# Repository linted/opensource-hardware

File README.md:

# opensource-hardware
Hardware creations for the masses

These files are under no warenty.

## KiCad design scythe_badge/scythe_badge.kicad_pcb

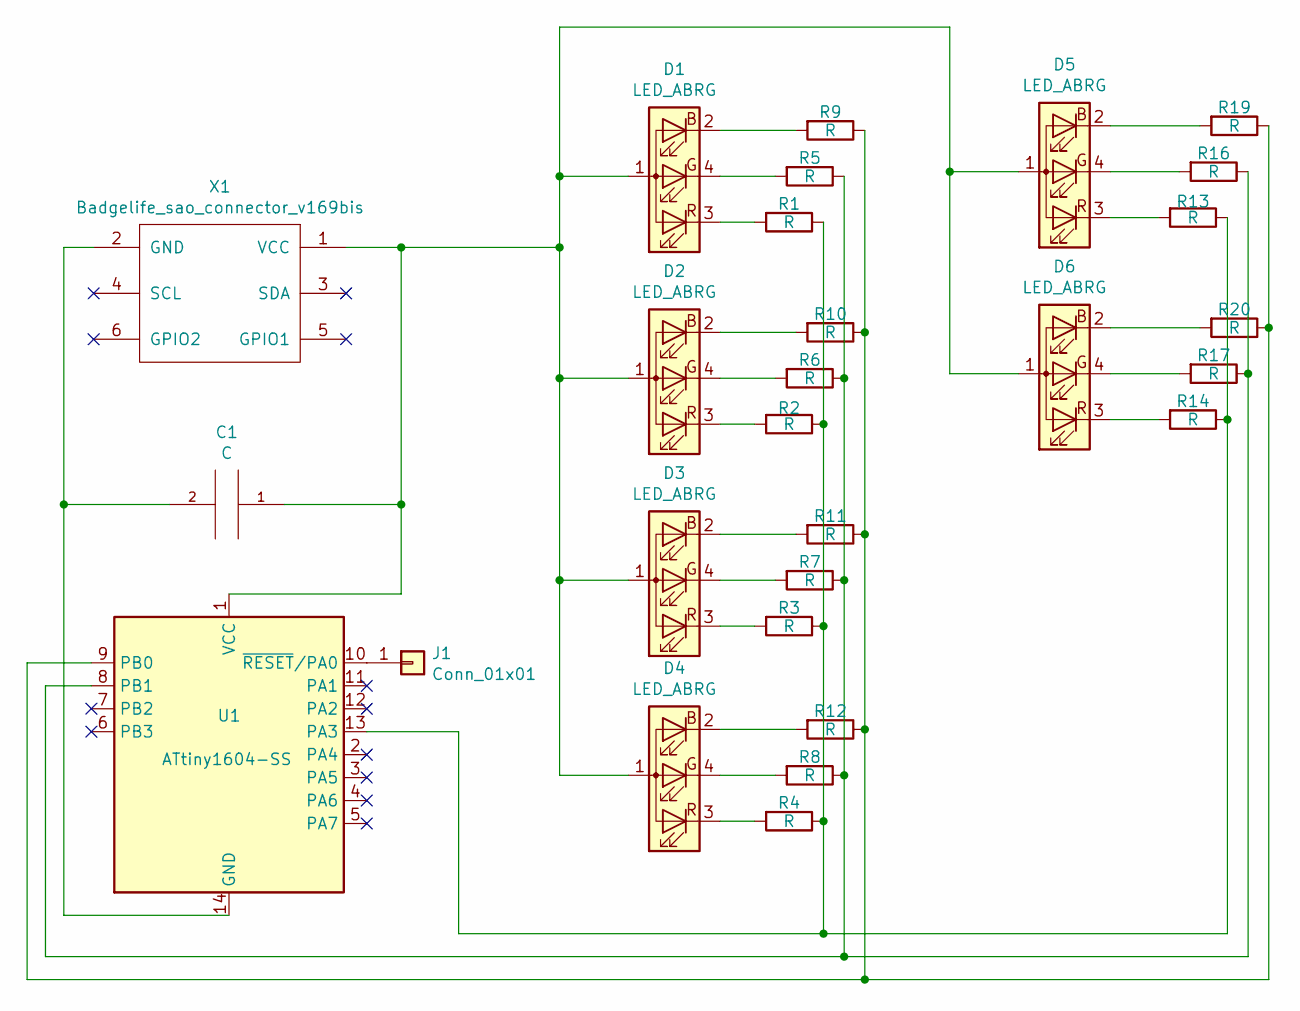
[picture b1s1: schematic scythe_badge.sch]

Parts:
C1: C; C_1206
D1, D2, D3, D4, D5, D6: LED_ABRG; E6C1204RGBC3UDA
J1: Conn_01x01; conn_01x01
R1, R2, R3, R4, R5, R6, R7, R8, R9, R10, R11, R12, R13, R14, R16, R17, R19, R20: R; R_0603
U1: ATtiny1604-SS; SOIC-14_3.9x8.7mm_P1.27mm
X1: Badgelife_sao_connector_v169bis; Badgelife-SAOv169-SAO-2x3

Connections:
unnamed: C1.1, D1.1 (A), D2.1 (A), D3.1 (A), D4.1 (A), D5.1 (A), D6.1 (A), U1.1 (VCC), X1.1 (VCC)
unnamed: C1.2, U1.14 (GND), X1.2 (GND)
unnamed: D1.2 (BK), R9.2
unnamed: D1.3 (RK), R1.2
unnamed: D1.4 (GK), R5.2
unnamed: D2.2 (BK), R10.2
unnamed: D2.3 (RK), R2.2
unnamed: D2.4 (GK), R6.2
unnamed: D3.2 (BK), R11.2
unnamed: D3.3 (RK), R3.2
unnamed: D3.4 (GK), R7.2
unnamed: D4.2 (BK), R12.2
unnamed: D4.3 (RK), R4.2
unnamed: D4.4 (GK), R8.2
unnamed: D5.2 (BK), R19.2
unnamed: D5.3 (RK), R13.2
unnamed: D5.4 (GK), R16.2
unnamed: D6.2 (BK), R20.2
unnamed: D6.3 (RK), R14.2
unnamed: D6.4 (GK), R17.2
unnamed: J1.1, U1.10 (~RESET~/PA0)
unnamed: R1.1, R2.1, R3.1, R4.1, R13.1, R14.1, U1.13 (PA3)
unnamed: R9.1, R10.1, R11.1, R12.1, R19.1, R20.1, U1.9 (PB0)
unnamed: R5.1, R6.1, R7.1, R8.1, R16.1, R17.1, U1.8 (PB1)

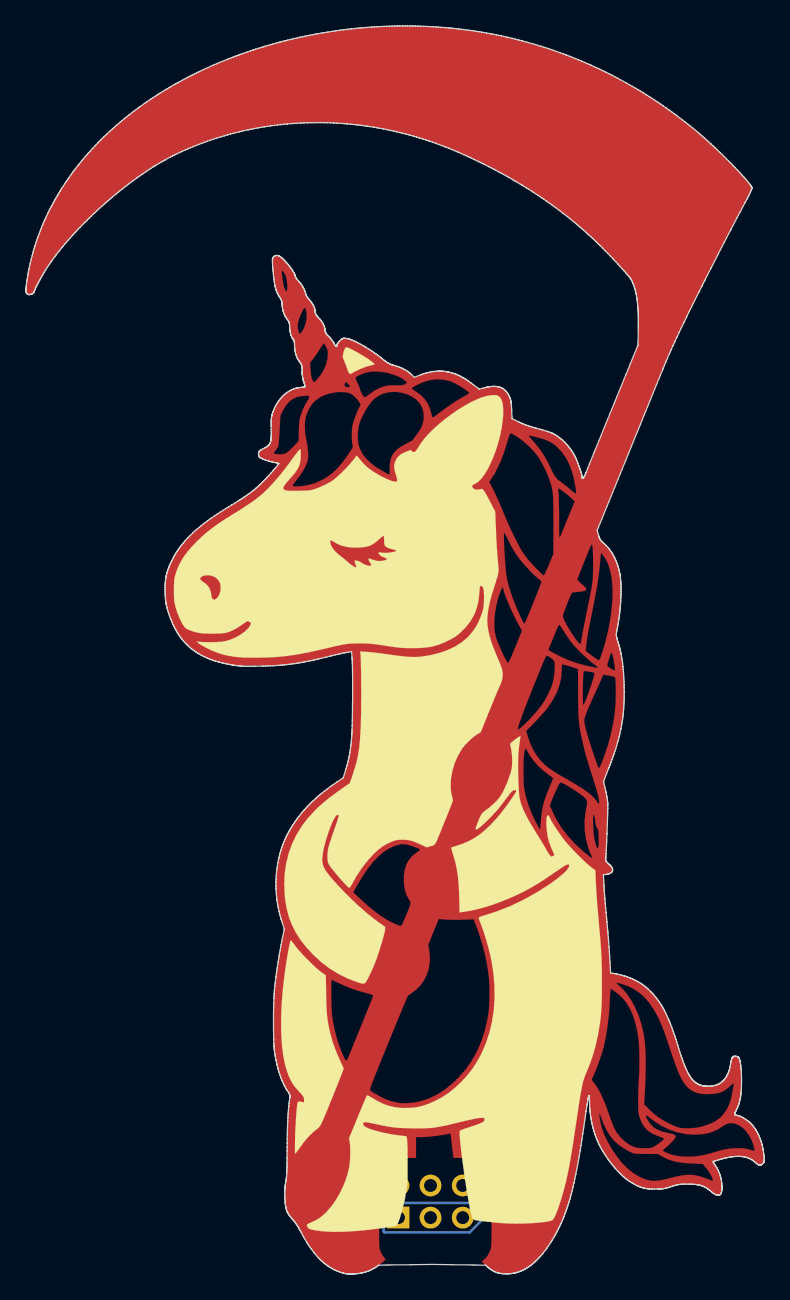
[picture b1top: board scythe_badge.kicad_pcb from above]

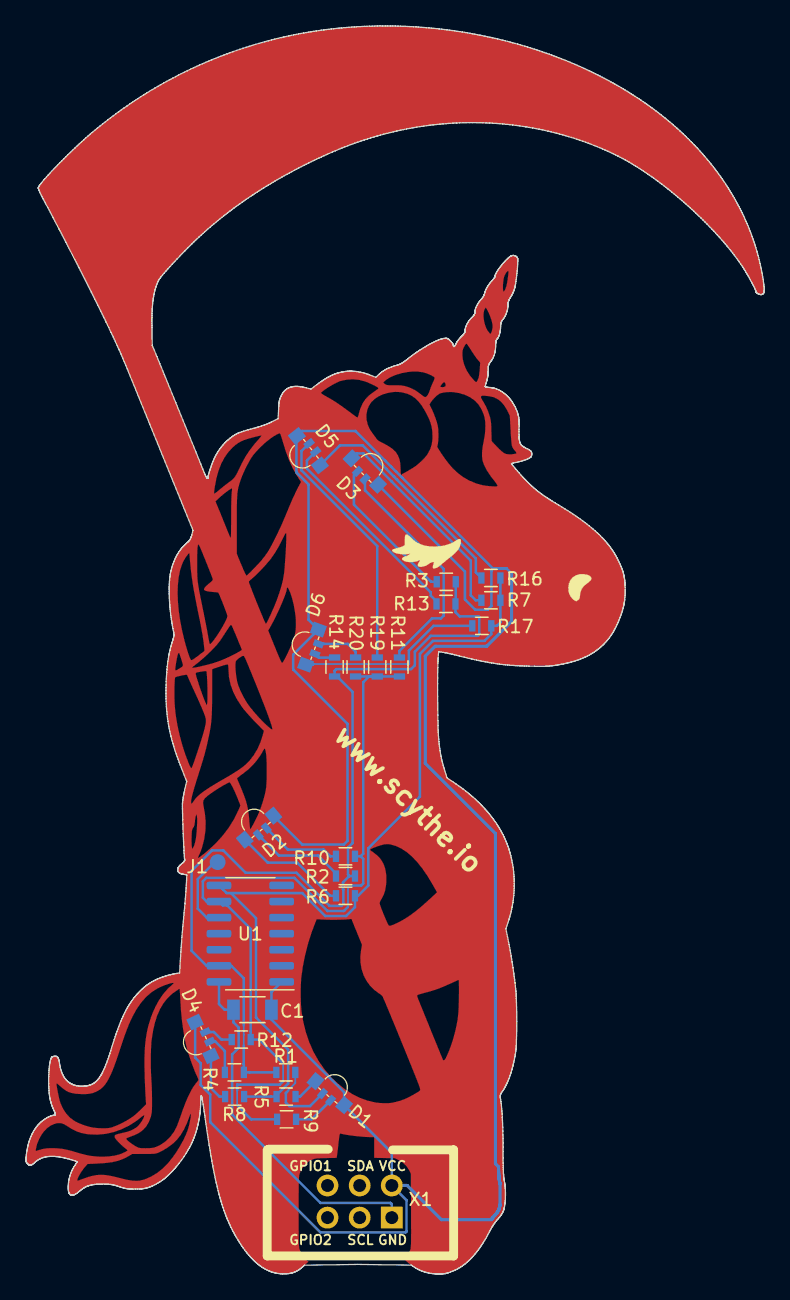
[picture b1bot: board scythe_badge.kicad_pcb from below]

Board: 2 copper layers, 58.3 x 98.6 mm, 29 parts (27 on the bottom side), 24 nets.

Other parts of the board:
Ref**: Val**; scythe_badge

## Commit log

2020-08-07 inital upload of scythe SAO
2020-08-07 fixed paths
